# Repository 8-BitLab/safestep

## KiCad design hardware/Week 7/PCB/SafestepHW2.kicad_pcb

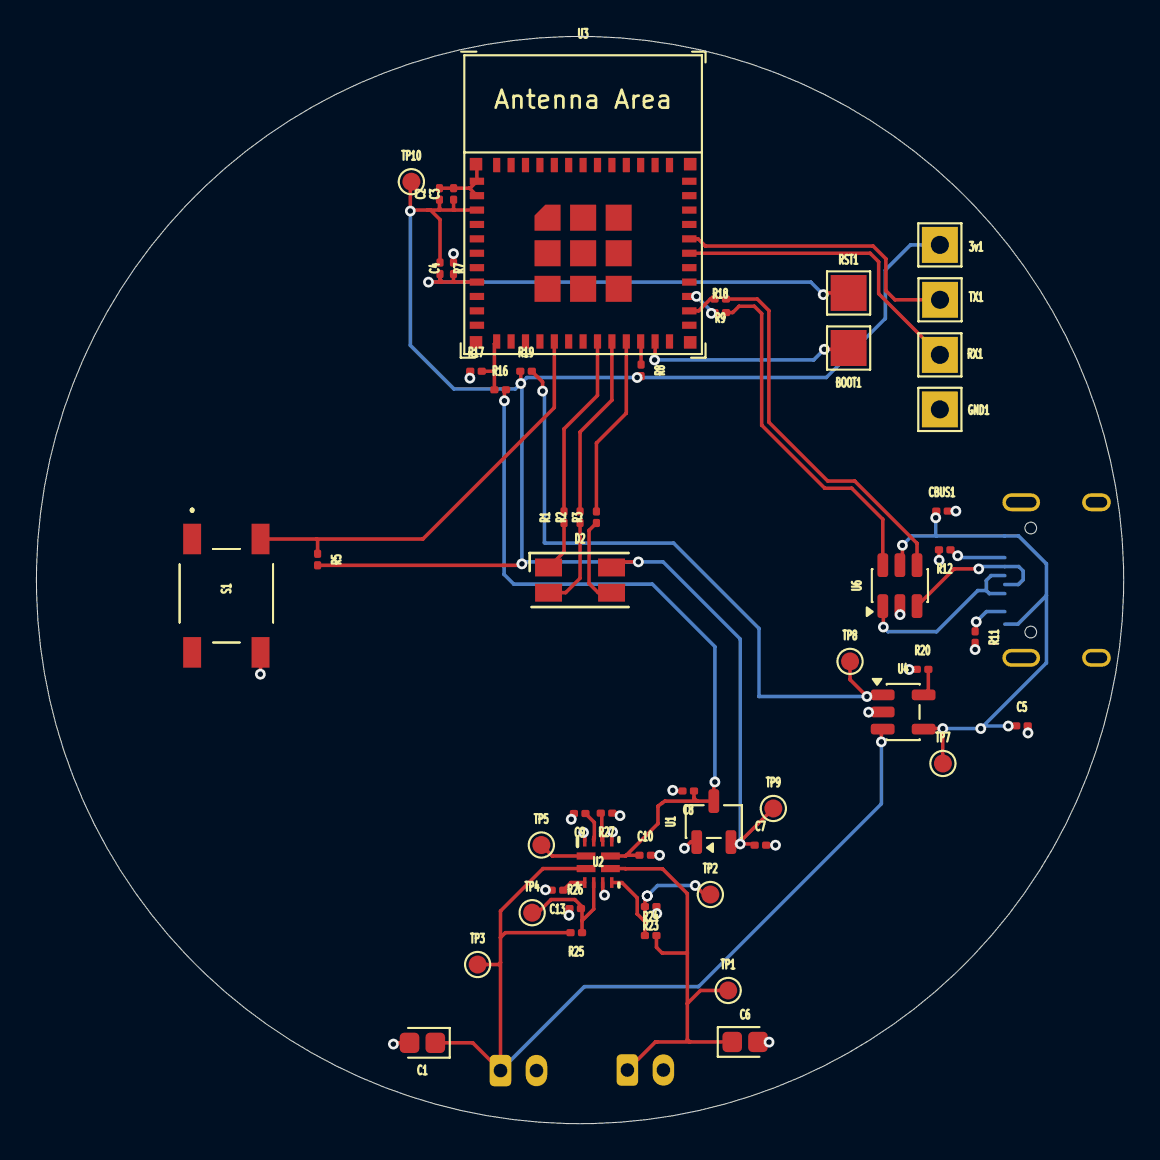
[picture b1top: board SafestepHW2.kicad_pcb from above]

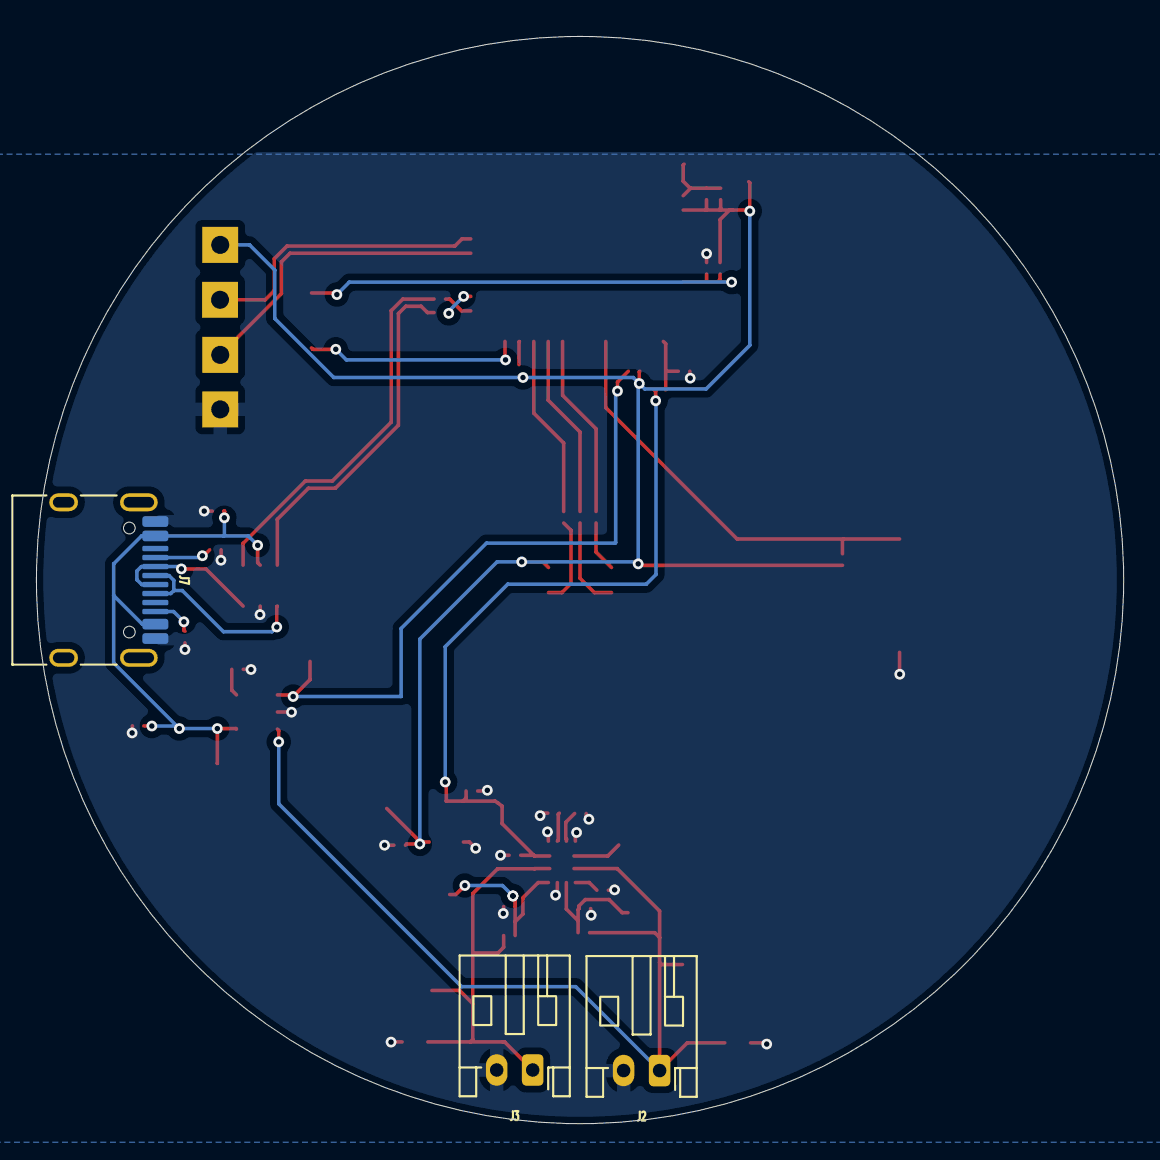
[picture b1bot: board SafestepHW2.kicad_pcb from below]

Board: 2 copper layers, 60.4 x 60.4 mm, 56 parts (3 on the bottom side), 34 nets.

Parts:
3v1: 3.3v; TestPoint_THTPad_2.0x2.0mm_Drill1.0mm
BOOT1: BOOT; TestPoint_Pad_2.0x2.0mm
C1, C6: 47µF; CP_EIA-1608-08_AVX-J
C2: 10μF; C_0201_0603Metric
C3: 0.1μF; C_0201_0603Metric
C4: 100nF; C_0201_0603Metric
C5, C10: 10µF; C_0201_0603Metric
C7, C8: 1μF; C_0201_0603Metric
C9, C13: 0.1µF; C_0201_0603Metric
CBUS1: 100nF; C_0201_0603Metric
D2: LED_RGBA; LED_RGB_1210
GND1: GND; TestPoint_THTPad_2.0x2.0mm_Drill1.0mm
J2: Li-Po 402025; JST_PH_S2B-PH-K_1x02_P2.00mm_Horizontal
J3: 3 x LR44; JST_PH_S2B-PH-K_1x02_P2.00mm_Horizontal
J7: USB-C; USB_C_Receptacle_HRO_TYPE-C-31-M-12
R1: 68Ω; R_0201_0603Metric
R2, R3: 33Ω; R_0201_0603Metric
R5, R7, R8, R19, R20, R26, R27: 10kΩ; R_0201_0603Metric
R9, R18: 22 Ω; R_0201_0603Metric
R11, R12: 5.1kΩ; R_0201_0603Metric
R16, R17: 330Ω; R_0201_0603Metric
R23: 30kΩ; R_0201_0603Metric
R24: 51kΩ; R_0201_0603Metric
R25: 14kΩ; R_0201_0603Metric
RST1: RST; TestPoint_Pad_2.0x2.0mm
RX1: Rx; TestPoint_THTPad_2.0x2.0mm_Drill1.0mm
S1: TL3342F160QG
TP1: IN1; TestPoint_Pad_D1.0mm
TP2: PR1; TestPoint_Pad_D1.0mm
TP3: IN2; TestPoint_Pad_D1.0mm
TP4: OV2; TestPoint_Pad_D1.0mm
TP5: P_OUT; TestPoint_Pad_D1.0mm
TP7: VBUS; TestPoint_Pad_D1.0mm
TP8: CHRG; TestPoint_Pad_D1.0mm
TP9: 3.3v; TestPoint_Pad_D1.0mm
TP10: 3.3v_IN; TestPoint_Pad_D1.0mm
TX1: Tx; TestPoint_THTPad_2.0x2.0mm_Drill1.0mm
U1: XC6206PxxxMR; SOT-23-3
U2: TPS2121RUXR; RUX0012A
U3: ESP32-C3-MINI-1
U4: TP4054; TSOT-23-5
U6: USBLC6-2SC6; SOT-23-6

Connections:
+3.3V OUT: 3v1.1 (Pin_1_1), C2.1, C3.1, C7.1, D2.4 (A), R5.2, R7.1, R8.2, R19.1, TP9.1 (1_1), TP10.1 (1_1), U1.2 (VO), U3.3 (3V3)
+3.7V: C1.1, J2.1, R25.2, TP3.1 (1_1), U2.2 (IN2), U4.3 (BAT)
+BATT: C6.1, J3.1, R24.2, TP1.1 (1_1), U2.7 (IN1)
/bb: D2.3 (BK), R3.1
/gg: D2.2 (GK), R2.1
/rr: D2.1 (RK), R1.1
B: R3.2, U3.21 (GPIO7)
BTN: R5.1, S1.3, U3.16 (GPIO10)
CHRG: R19.2, TP8.1 (1_1), U3.13 (GPIO1/ADC1_CH1/XTAL_32K_N), U4.1 (~CHRG)
G: R2.2, U3.20 (GPIO6)
GND: C1.2, C2.2, C3.2, C4.2, C5.2, C6.2, C7.2, C8.2, C9.2, C10.2, C13.2, CBUS1.2, GND1.1 (Pin_1_1), J2.2, J3.2, J7.A1 (GND), J7.A12 (GND), J7.B1 (GND), J7.B12 (GND), R11.2, R12.2, R17.1, R20.1, R23.1, R26.1, R27.1, S1.4, U1.1 (GND), U2.5 (OV1), U2.9 (ST), U2.12 (GND), U3.1 (GND), U3.2 (GND), U3.11 (GND), U3.14 (GND), U3.36 (GND), U3.37 (GND), U3.38 (GND), U3.39 (GND), U3.40 (GND), U3.41 (GND), U3.42 (GND), U3.43 (GND), U3.44 (GND), U3.45 (GND), U3.46 (GND), U3.47 (GND), U3.48 (GND), U3.49 (GND), U3.50 (GND), U3.51 (GND), U3.52 (GND), U3.53 (GND), U4.2 (GND), U6.2 (GND)
LVL: R16.1, R17.2, U3.12 (GPIO0/ADC1_CH0/XTAL_32K_P)
unnamed: BOOT1.1 (Pin_1_1), U3.23 (GPIO9)
unnamed: J7.A5 (CC1), R12.1
unnamed: J7.B5 (CC2), R11.1
unnamed: C4.1, R7.2, RST1.1 (Pin_1_1), U3.8 (EN/CHIP_PU)
unnamed: C13.1, U2.3 (CP2)
unnamed: R27.2, U2.10 (ILM)
unnamed: R25.1, R26.2, TP4.1 (1_1), U2.4 (OV2)
unnamed: R23.2, R24.1, TP2.1 (1_1), U2.6 (PR1)
unnamed: C9.1, U2.11 (SS)
unnamed: R8.1, U3.22 (GPIO8)
unnamed: R9.2, U3.26 (GPIO18/USB_D-)
unnamed: R18.1, U3.27 (GPIO19/USB_D+)
unnamed: R20.2, U4.5 (PROG)
P_OUT: C8.1, C10.1, R16.2, TP5.1 (1_1), U1.3 (VI), U2.1 (OUT), U2.8 (OUT)
R: R1.2, U3.19 (GPIO5/ADC2_CH0)
RX: RX1.1 (Pin_1_1), U3.30 (GPIO20/U0RXD)
TX: TX1.1 (Pin_1_1), U3.31 (GPIO21/U0TXD)
UD+: J7.A6 (D+), J7.B6 (D+), U6.1 (I/O1)
UD-: J7.A7 (D-), J7.B7 (D-), U6.3 (I/O2)
USB_D+: R18.2, U6.6 (I/O1)
USB_D-: R9.1, U6.4 (I/O2)
VBUS: C5.1, CBUS1.1, J7.A4 (VBUS), J7.A9 (VBUS), J7.B4 (VBUS), J7.B9 (VBUS), TP7.1 (1_1), U4.4 (V_{CC}), U6.5 (VBUS)

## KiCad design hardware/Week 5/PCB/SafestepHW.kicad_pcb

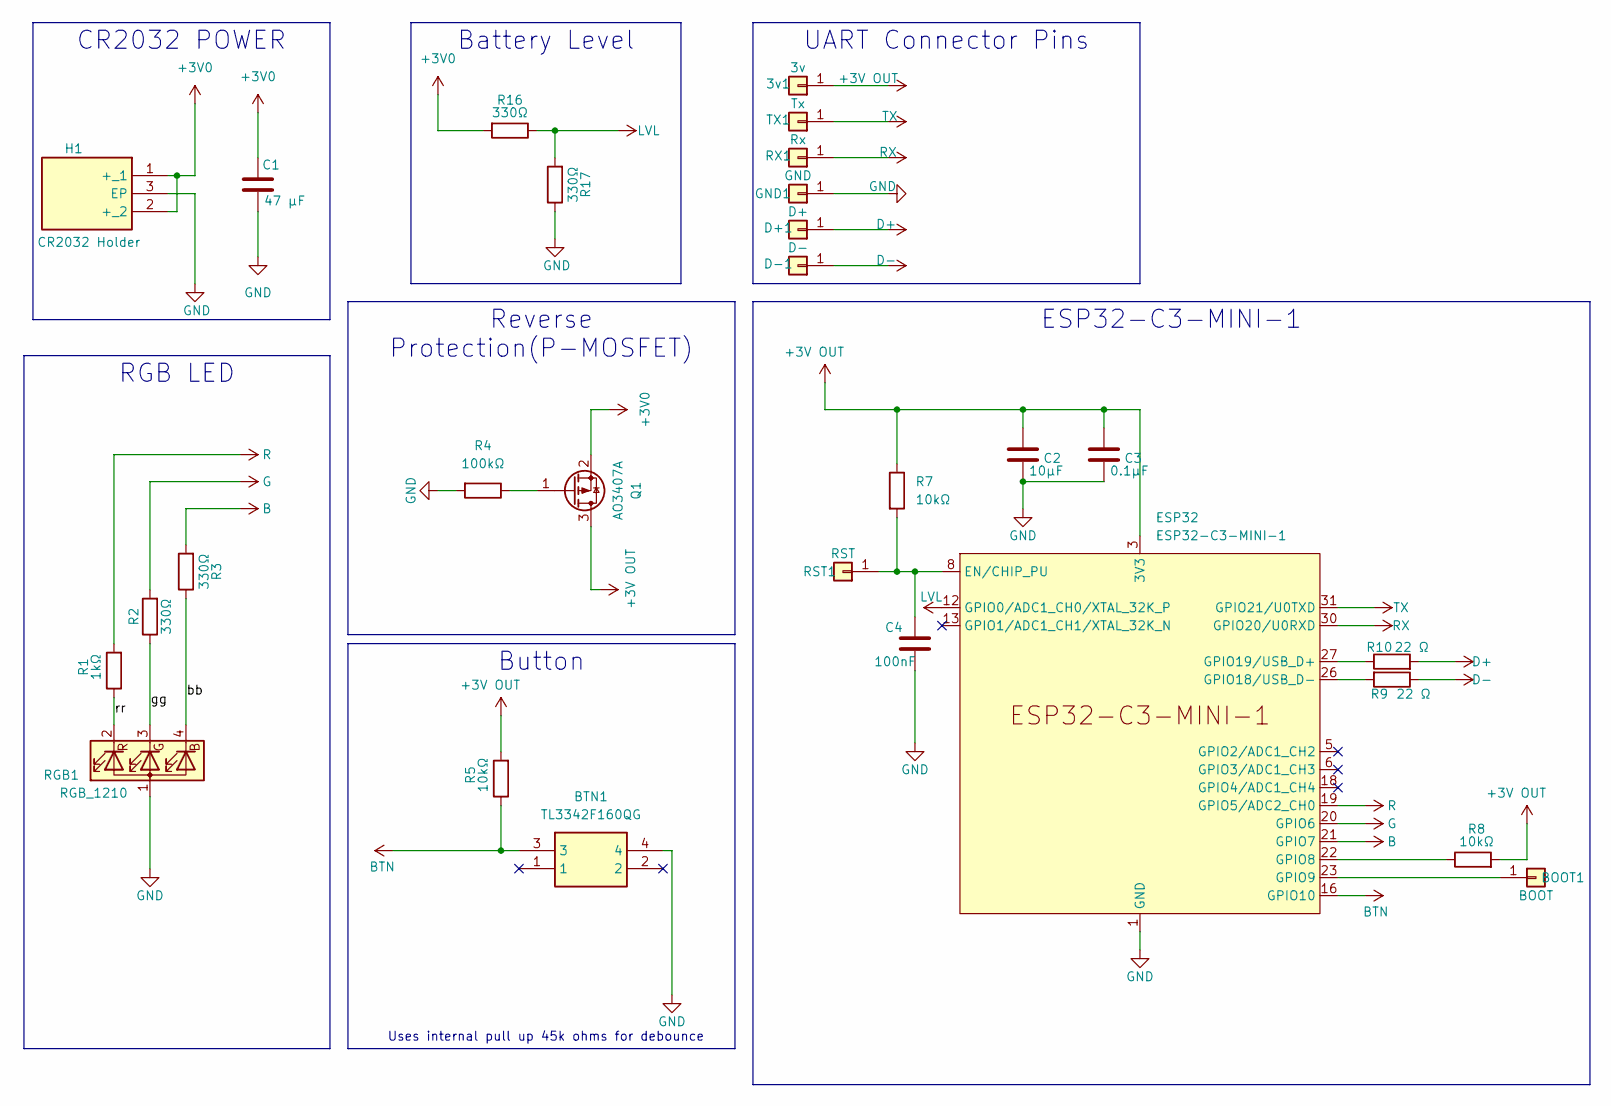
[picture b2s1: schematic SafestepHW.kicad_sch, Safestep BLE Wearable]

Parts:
3v1: 3v; TestPoint_THTPad_2.0x2.0mm_Drill1.0mm
BOOT1: BOOT; TestPoint_Pad_2.0x2.0mm
BTN1: TL3342F160QG; Mouser Part Number 612-TL3342F160
C1: 47 µF; C_01005_0402Metric
C2: 10μF; C_01005_0402Metric
C3: 0.1μF; C_01005_0402Metric
C4: 100nF; C_01005_0402Metric
D+1: D+; TestPoint_THTPad_2.0x2.0mm_Drill1.0mm
D-1: D-; TestPoint_THTPad_2.0x2.0mm_Drill1.0mm
ESP32: ESP32-C3-MINI-1
GND1: GND; TestPoint_THTPad_2.0x2.0mm_Drill1.0mm
H1: CR2032 Holder; BATHLD003SMT; Mouser Part Number 712-BAT-HLD-003-SMT
Q1: AO3407A; SOT-23
R1: 1kΩ; R_01005_0402Metric
R2, R3, R16, R17: 330Ω; R_01005_0402Metric
R4: 100kΩ; R_01005_0402Metric
R5, R7, R8: 10kΩ; R_01005_0402Metric
R9, R10: 22 Ω; R_01005_0402Metric
RGB1: RGB_1210; LED_RGB_1210
RST1: RST; TestPoint_Pad_2.0x2.0mm
RX1: Rx; TestPoint_THTPad_2.0x2.0mm_Drill1.0mm
TX1: Tx; TestPoint_THTPad_2.0x2.0mm_Drill1.0mm

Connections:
+3V0: C1.1, H1.1 (+_1), H1.2 (+_2), Q1.2 (S), R16.2
+3V OUT: 3v1.1 (Pin_1_1), C2.1, C3.1, ESP32.3 (3V3), Q1.3 (D), R5.2, R7.1, R8.2
/bb: R3.1, RGB1.4 (BK)
/gg: R2.1, RGB1.3 (GK)
/rr: R1.1, RGB1.2 (RK)
B: ESP32.21 (GPIO7), R3.2
BTN: BTN1.3, ESP32.16 (GPIO10), R5.1
D+: D+1.1 (Pin_1_1), R10.2
D-: D-1.1 (Pin_1_1), R9.1
G: ESP32.20 (GPIO6), R2.2
GND: BTN1.4, C1.2, C2.2, C3.2, C4.2, ESP32.1 (GND), ESP32.2 (GND), ESP32.11 (GND), ESP32.14 (GND), ESP32.36 (GND), ESP32.37 (GND), ESP32.38 (GND), ESP32.39 (GND), ESP32.40 (GND), ESP32.41 (GND), ESP32.42 (GND), ESP32.43 (GND), ESP32.44 (GND), ESP32.45 (GND), ESP32.46 (GND), ESP32.47 (GND), ESP32.48 (GND), ESP32.49 (GND), ESP32.50 (GND), ESP32.51 (GND), ESP32.52 (GND), ESP32.53 (GND), GND1.1 (Pin_1_1), H1.3 (EP), R4.2, R17.1, RGB1.1 (A)
LVL: ESP32.12 (GPIO0/ADC1_CH0/XTAL_32K_P), R16.1, R17.2
unnamed: BOOT1.1 (Pin_1_1), ESP32.23 (GPIO9)
unnamed: C4.1, ESP32.8 (EN/CHIP_PU), R7.2, RST1.1 (Pin_1_1)
unnamed: ESP32.22 (GPIO8), R8.1
unnamed: ESP32.26 (GPIO18/USB_D-), R9.2
unnamed: ESP32.27 (GPIO19/USB_D+), R10.1
unnamed: Q1.1 (G), R4.1
R: ESP32.19 (GPIO5/ADC2_CH0), R1.2
RX: ESP32.30 (GPIO20/U0RXD), RX1.1 (Pin_1_1)
TX: ESP32.31 (GPIO21/U0TXD), TX1.1 (Pin_1_1)

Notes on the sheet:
Uses internal pull up 45k ohms for debounce
ESP32-C3-MINI-1
CR2032 POWER
UART Connector Pins
Button
Reverse Protection(P-MOSFET)
Battery Level
RGB LED

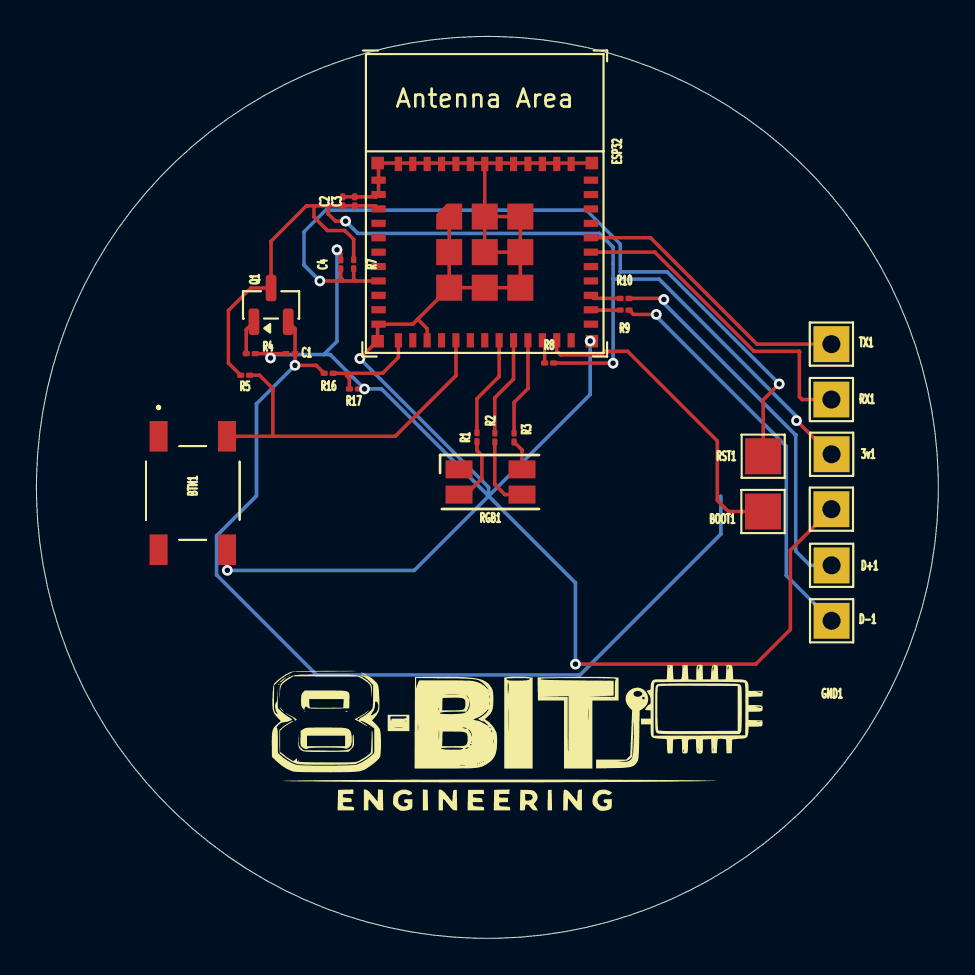
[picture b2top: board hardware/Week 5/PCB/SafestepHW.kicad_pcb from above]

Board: 2 copper layers, 50.1 x 50.1 mm, 28 parts (1 on the bottom side), 21 nets.

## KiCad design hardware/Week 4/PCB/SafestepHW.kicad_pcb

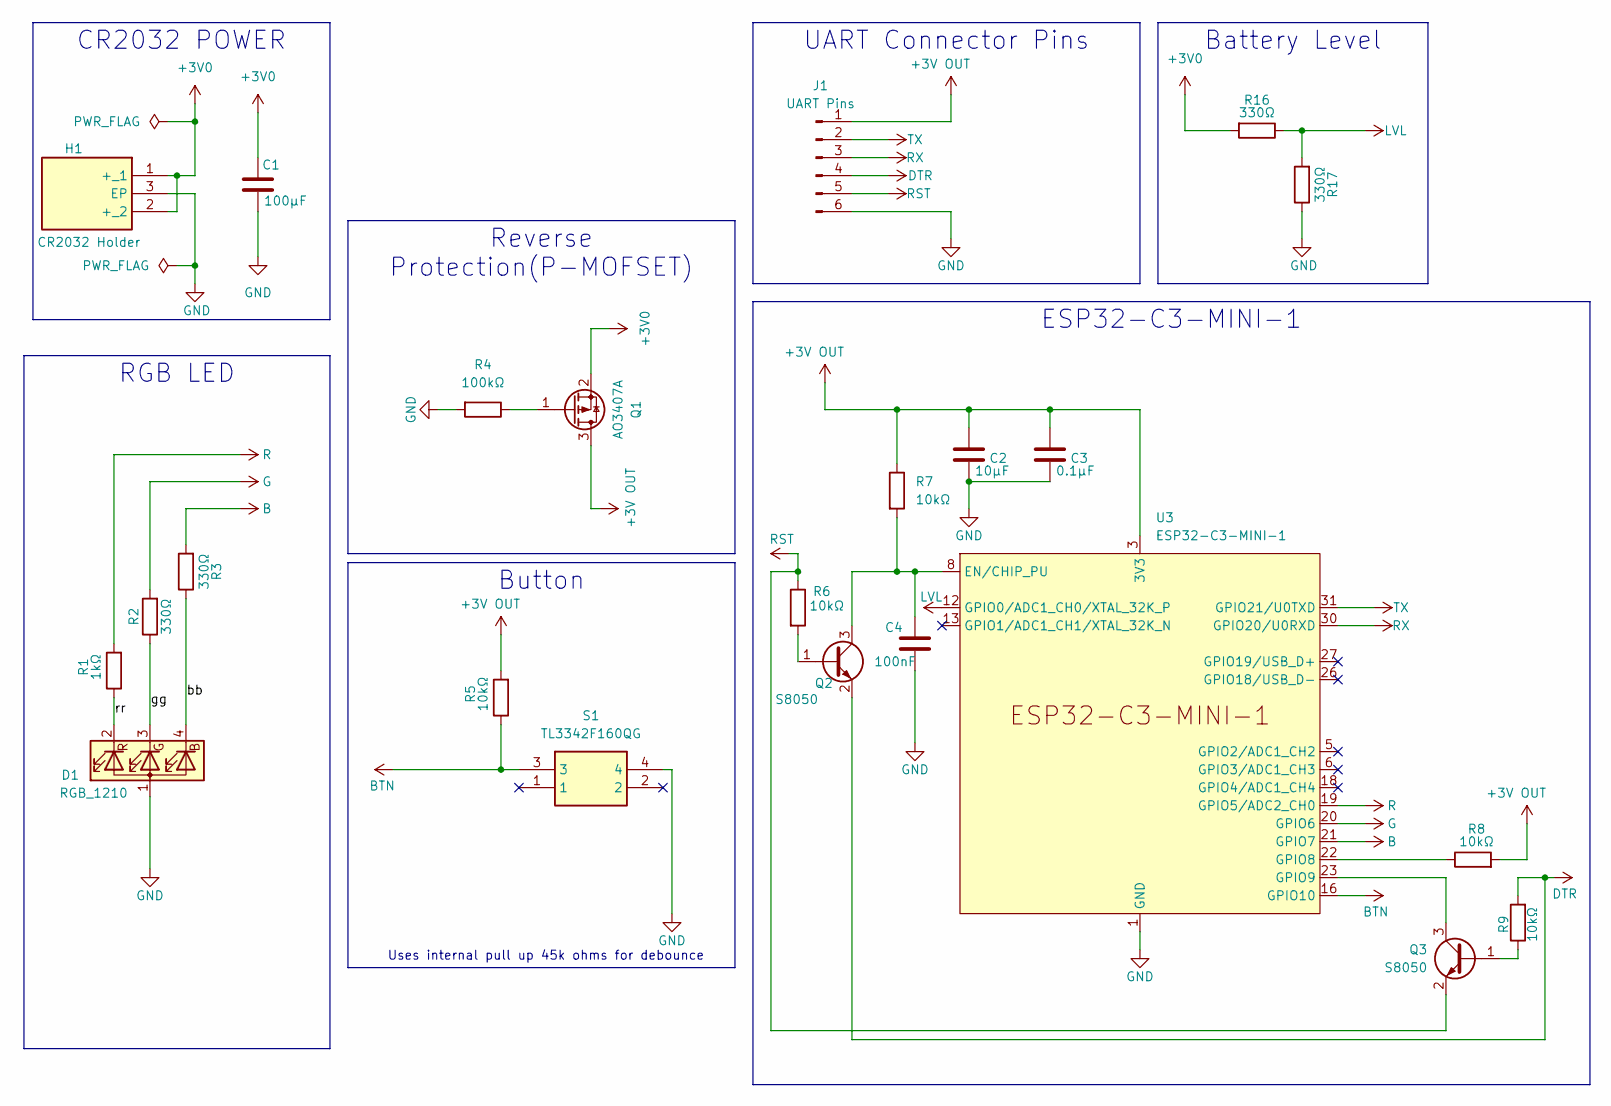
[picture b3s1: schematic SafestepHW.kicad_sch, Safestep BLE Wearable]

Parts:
C1: 100µF; C_01005_0402Metric
C2: 10μF; C_01005_0402Metric
C3: 0.1μF; C_01005_0402Metric
C4: 100nF; C_01005_0402Metric
D1: RGB_1210; LED_RGB_1210
H1: CR2032 Holder; BATHLD003SMT; Mouser Part Number 712-BAT-HLD-003-SMT
J1: UART Pins; PinHeader_1x06_P2.54mm_Vertical
Q1: AO3407A; SOT-23
Q2, Q3: S8050; SOT-23
R1: 1kΩ; R_01005_0402Metric
R2, R3, R16, R17: 330Ω; R_01005_0402Metric
R4: 100kΩ; R_01005_0402Metric
R5, R6, R7, R8, R9: 10kΩ; R_01005_0402Metric
S1: TL3342F160QG; Mouser Part Number 612-TL3342F160
U3: ESP32-C3-MINI-1

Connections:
+3V0: C1.1, H1.1 (+_1), H1.2 (+_2), Q1.2 (S), R16.2
+3V OUT: C2.1, C3.1, J1.1, Q1.3 (D), R5.2, R7.1, R8.2, U3.3 (3V3)
/bb: D1.4 (BK), R3.1
/gg: D1.3 (GK), R2.1
/rr: D1.2 (RK), R1.1
B: R3.2, U3.21 (GPIO7)
BTN: R5.1, S1.3, U3.16 (GPIO10)
DTR: J1.4, Q2.2 (E), R9.2
G: R2.2, U3.20 (GPIO6)
GND: C1.2, C2.2, C3.2, C4.2, D1.1 (A), H1.3 (EP), J1.6, R4.2, R17.1, S1.4, U3.1 (GND), U3.2 (GND), U3.11 (GND), U3.14 (GND), U3.36 (GND), U3.37 (GND), U3.38 (GND), U3.39 (GND), U3.40 (GND), U3.41 (GND), U3.42 (GND), U3.43 (GND), U3.44 (GND), U3.45 (GND), U3.46 (GND), U3.47 (GND), U3.48 (GND), U3.49 (GND), U3.50 (GND), U3.51 (GND), U3.52 (GND), U3.53 (GND)
LVL: R16.1, R17.2, U3.12 (GPIO0/ADC1_CH0/XTAL_32K_P)
unnamed: Q1.1 (G), R4.1
unnamed: Q2.1 (B), R6.2
unnamed: C4.1, Q2.3 (C), R7.2, U3.8 (EN/CHIP_PU)
unnamed: Q3.1 (B), R9.1
unnamed: Q3.3 (C), U3.23 (GPIO9)
unnamed: R8.1, U3.22 (GPIO8)
R: R1.2, U3.19 (GPIO5/ADC2_CH0)
RST: J1.5, Q3.2 (E), R6.1
RX: J1.3, U3.30 (GPIO20/U0RXD)
TX: J1.2, U3.31 (GPIO21/U0TXD)

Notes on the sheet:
Uses internal pull up 45k ohms for debounce
ESP32-C3-MINI-1
CR2032 POWER
Button
UART Connector Pins
Reverse Protection(P-MOFSET)
Battery Level
RGB LED

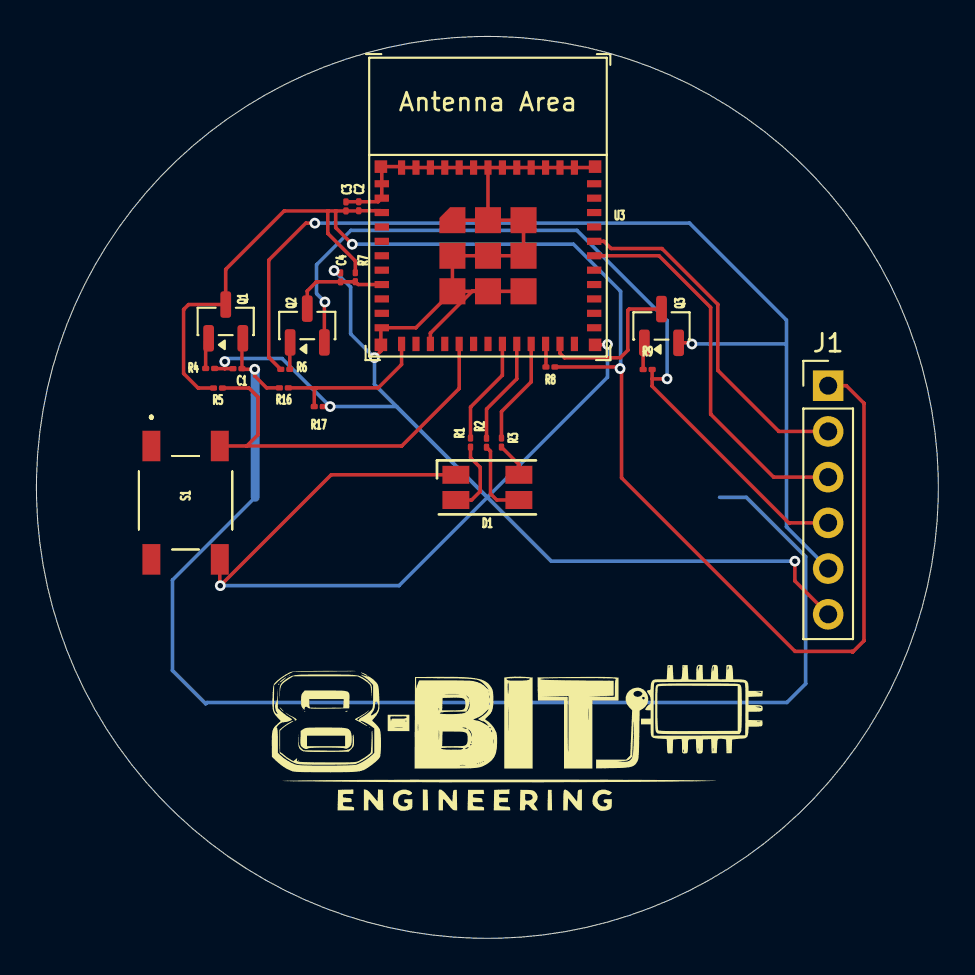
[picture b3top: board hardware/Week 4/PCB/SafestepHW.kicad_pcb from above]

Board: 2 copper layers, 50.1 x 50.1 mm, 23 parts (1 on the bottom side), 21 nets.

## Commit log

2026-04-04 feat: add SafeStepMessage model and MessageParser service
2026-04-13 Added basic receiver (+RSSI stats)
2026-04-13 Add basic advertiser.
2026-04-20 Week 3 HW Update
2026-04-28 Added uart communication into main dongle program
2026-04-28 feat(desktop): add Firebase cloud mode and local push integration
2026-05-02 Week 4 & 5 HW Update
2026-05-05 style: redesign SafeStep desktop app UI
2026-05-11 Week 6 HW Update
2026-05-17 Week 7 HW Update
2026-06-02 Fix BLE friendly name input and improve quick action command handling
